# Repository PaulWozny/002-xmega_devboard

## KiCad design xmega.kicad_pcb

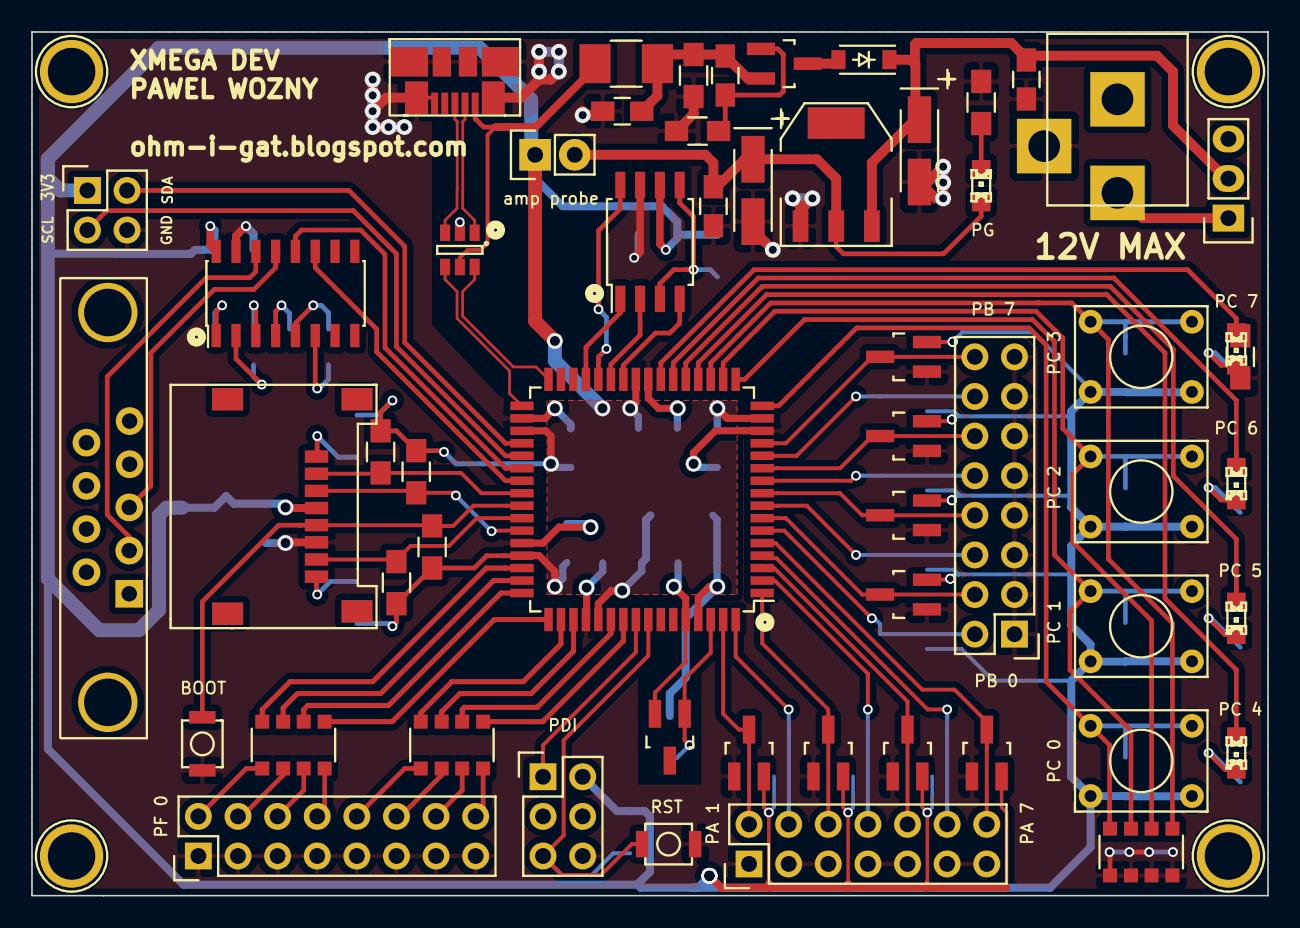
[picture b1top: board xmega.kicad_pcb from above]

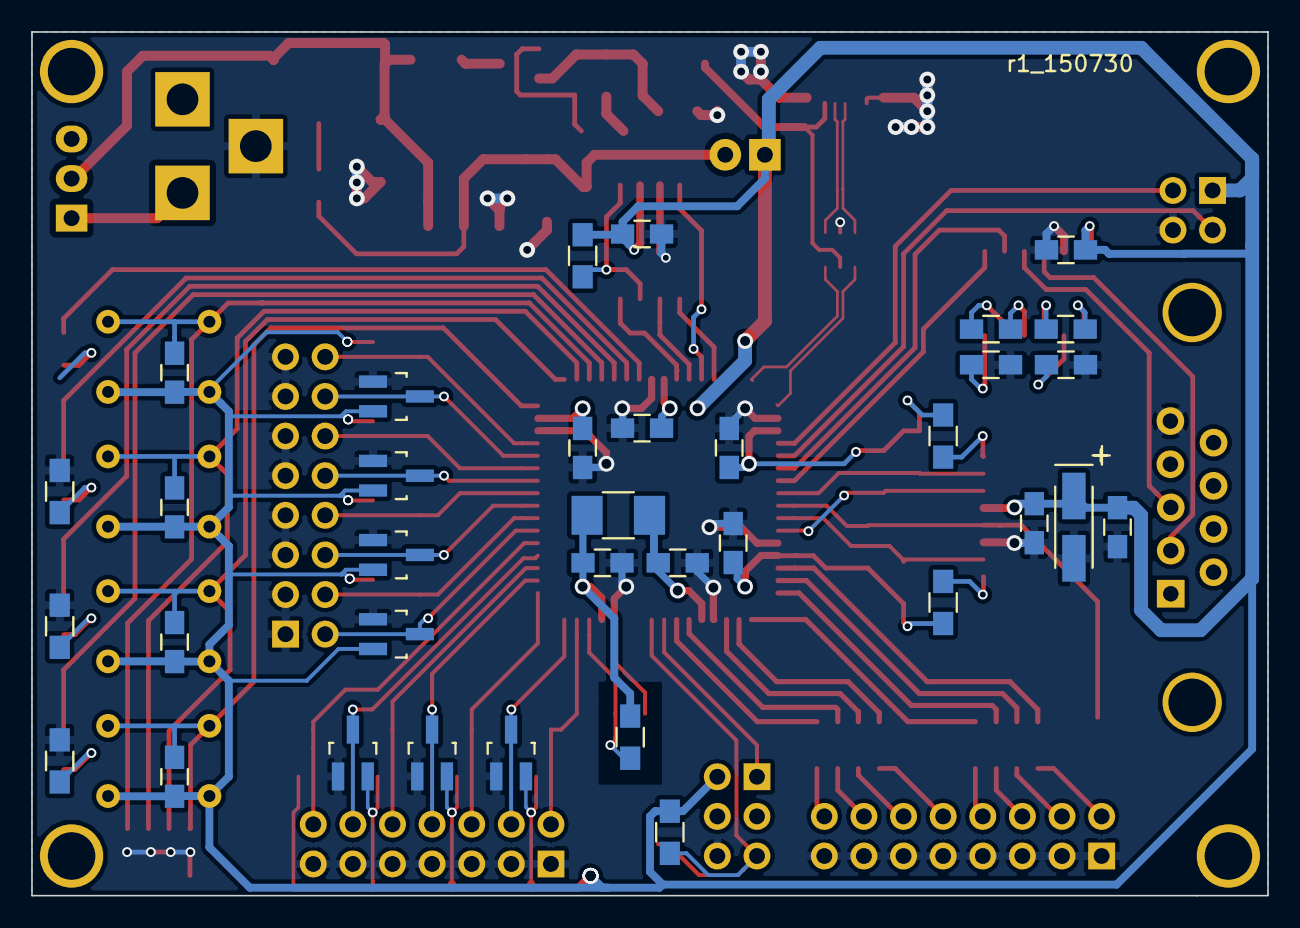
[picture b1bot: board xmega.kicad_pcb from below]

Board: 2 copper layers, 79.2 x 55.4 mm, 91 parts (35 on the bottom side), 84 nets.

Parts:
C1, C2, C3, C5, C6, C7, C8, C9, C10, C11, C12, C13, C15, C16, C17, C18, C19, C20, C21, C22, C23: 100n; C_0805_HandSoldering
C14: 1n; C_0805_HandSoldering
CT1, CT2, CT3: 100u; TantalC_SizeA_EIA-3216_HandSoldering
D2: SS14; SOD-123
D3: PG3.3; LED-0805
D4, D5, D6, D7, D8, D9, D10, D11, D12, D13, D14, D15, D16, D17, D18: Dprot; SOT-23_Handsoldering
D19, D20, D21, D22: LED; LED-0805
IC1: ATXMEGA128A3U-A; TQFP-64_14x14mm_Pitch0.8mm
L1, L2: 10u; R_1210_HandSoldering
P1: PH_PWR; BARREL_JACK
P2: PH_PDI; Pin_Header_Straight_2x03
P3: PH_CURRENT; Pin_Header_Straight_1x02
P4: PH_DIGITAL IO; Pin_Header_Straight_2x08
P5: USB_OTG; uUSB__G3515-10
P6: PH_PA; Pin_Header_Straight_2x07
P7: CONN_01X16; Pin_Header_Straight_2x08
P8: PH_TWI; Pin_Header_Straight_2x02
Q1: SI2323DS; SOT-23_Handsoldering
R1, R2: 22k; R_0805_HandSoldering
R3, R4: 100k; R_0805_HandSoldering
R6, R14, R15, R16, R17: 220; R_0805_HandSoldering
R7: 17k8; R_0805_HandSoldering
R8, R9, R10, R11, R12, R13: 50K; R_0805_HandSoldering
RPC1: 100k; R_Array_Convex_4x1206
RPF1, RPF2: 220; R_Array_Convex_4x1206
SW1: boot; SWITCH__B3U-1000P
SW2: rst; SWITCH__B3U-1000P
SW3: SPST; Pin_Header_Straight_1x03
SW4, SW5, SW6, SW7: TACTB-24R-F; SWITCH__B3F-1022
U1: AT45DB161E - EIAJ SOIC; SOIJ-8_5.3x5.3mm_Pitch1.27mm
U2: AP1117; SOT-223
U3: LM4040BIM3-2.5; SOT-23_Handsoldering
U4: USBLC62; SOT-23-6
U5: micro_sd_card; SDcard__112C-TBAR-R02
U6: MAX3232EID; SOIC-16_3.9x9.9mm_Pitch1.27mm
USART1: DBR09F; USART__DBR09F

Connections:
+3.3VADC: C11.1, IC1.61, L1.2, R7.1
+3V3: C5.1, C6.1, C7.1, C8.1, C9.1, C10.1, C13.1, C14.1, C15.1, C16.1, C17.1, C18.1, C21.2, CT3.1, D4.2, D5.2, D6.2, D7.2, D8.2, D9.2, D10.2, D11.2, D12.2, D13.2, D14.2, D15.2, D16.2, D17.2, D18.2, IC1.15, IC1.25, IC1.35, IC1.45, IC1.53, L1.1, P2.2, P3.1, P8.1, R1.1, R2.1, R8.1, R9.1, R10.1, R11.1, R12.1, R13.1, SW4.2, SW5.2, SW6.2, SW7.2, U1.6, U5.4, U6.16
+5V: C1.1, C12.1, L2.1, Q1.2, R3.1
/Dpa/IO1: D4.3, IC1.63, P6.2
/Dpa/IO2: D5.3, IC1.64, P6.4
/Dpa/IO3: D6.3, IC1.1, P6.6
/Dpa/IO4: D7.3, IC1.2, P6.8
/Dpa/IO5: D8.3, IC1.3, P6.10
/Dpa/IO6: D9.3, IC1.4, P6.12
/Dpa/IO7: D10.3, IC1.5, P6.14
/Dpb/IO0: D11.3, IC1.6, P7.2
/Dpb/IO1: D12.3, IC1.7, P7.4
/Dpb/IO2: D13.3, IC1.8, P7.6
/Dpb/IO3: D14.3, IC1.9, P7.8
/Dpb/IO4: D15.3, IC1.10, P7.10
/Dpb/IO5: D16.3, IC1.11, P7.12
/Dpb/IO6: D17.3, IC1.12, P7.14
/Dpb/IO7: D18.3, IC1.13, P7.16
/RLadConn/in0: IC1.46, RPF1.8
/RLadConn/in1: IC1.47, RPF1.7
/RLadConn/in2: IC1.48, RPF1.6
/RLadConn/in3: IC1.49, RPF1.5
/RLadConn/in4: IC1.50, RPF2.8
/RLadConn/in5: IC1.51, RPF2.7
/RLadConn/in6: IC1.54, RPF2.6
/RLadConn/in7: IC1.55, RPF2.5
/SD_CARD/MISO: IC1.42, R9.2, U5.7
/SD_CARD/MOSI: IC1.43, R11.2, U5.3
/SD_CARD/SCK: IC1.41, R10.2, SW1.2, U5.5
/SD_CARD/~SS: IC1.40, R12.2, U5.2
/USB/D1+: P5.3, U4.3
/USB/D1-: P5.2, U4.1
/USB/D2+: IC1.33, U4.4
/USB/D2-: IC1.32, U4.6
/Vcc_5_3V/CC0: C3.1, CT2.1, D3.2, P3.2, U2.2
/Vcc_5_3V/PWR+: P1.1, SW3.1
/buttons/O0: C15.2, IC1.16, RPC1.4, SW4.1
/buttons/O1: C16.2, IC1.17, RPC1.3, SW5.1
/buttons/O2: C17.2, IC1.18, RPC1.2, SW6.1
/buttons/O3: C18.2, IC1.19, RPC1.1, SW7.1
/diode/diode0: D22.2, IC1.20
/diode/diode1: D21.2, IC1.21
/diode/diode2: D20.2, IC1.22
/diode/diode3: D19.2, IC1.23
/twi/SCL: IC1.37, P8.3
/twi/SDA: IC1.36, P8.2
/usart/rx1: IC1.38, U6.12
/usart/tx1: IC1.39, U6.11
/vrefA/Vref: IC1.62, R7.2, U3.1
GND: C2.2, C3.2, C5.2, C6.2, C7.2, C8.2, C9.2, C10.2, C11.2, C12.2, C13.2, C14.2, C21.1, C22.1, C23.1, CT1.2, CT2.2, CT3.2, D4.1, D5.1, D6.1, D7.1, D8.1, D9.1, D10.1, D11.1, D12.1, D13.1, D14.1, D15.1, D16.1, D17.1, D18.1, IC1.14, IC1.24, IC1.34, IC1.44, IC1.52, IC1.60, P1.3, P2.6, P4.1, P4.3, P4.5, P4.7, P4.9, P4.11, P4.13, P4.15, P5.5, P5.6, P6.1, P6.3, P6.5, P6.7, P6.9, P6.11, P6.13, P7.1, P7.3, P7.5, P7.7, P7.9, P7.11, P7.13, P7.15, P8.4, R3.2, R4.2, R6.2, R14.2, R15.2, R16.2, R17.2, RPC1.5, RPC1.6, RPC1.7, RPC1.8, SW1.1, SW2.1, U1.7, U2.1, U3.2, U4.2, U5.6, U6.15, USART1.5
unnamed: C1.2, Q1.1, R4.1
unnamed: C2.1, CT1.1, D2.1, SW3.2, U2.3
unnamed: C19.1, U6.1
unnamed: C19.2, U6.3
unnamed: C20.1, U6.4
unnamed: C20.2, U6.5
unnamed: C22.2, U6.2
unnamed: C23.2, U6.6
unnamed: D2.2, Q1.3
unnamed: D3.1, R6.1
unnamed: D19.1, R14.1
unnamed: D20.1, R15.1
unnamed: D21.1, R16.1
unnamed: D22.1, R17.1
unnamed: IC1.26, U1.4
unnamed: IC1.27, U1.2
unnamed: IC1.28, U1.8
unnamed: IC1.29, U1.1
unnamed: L2.2, P5.1, U4.5
unnamed: P4.2, RPF1.1
unnamed: P4.4, RPF1.2
unnamed: P4.6, RPF1.3
unnamed: P4.8, RPF1.4
unnamed: P4.10, RPF2.1
unnamed: P4.12, RPF2.2
unnamed: P4.14, RPF2.3
unnamed: P4.16, RPF2.4
unnamed: R2.2, U1.3, U1.5
unnamed: R8.2, U5.8
unnamed: R13.2, U5.1
unnamed: U6.13, USART1.3
unnamed: U6.14, USART1.2
PDI_CLK: IC1.57, P2.5, R1.2, SW2.2
PDI_DATA: IC1.56, P2.1

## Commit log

2015-07-03 :tada: Added .gitattributes
2015-07-03 REV1
    dev board
    usb,usart,twi, PDI...
